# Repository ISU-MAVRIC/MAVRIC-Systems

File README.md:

# MAVRIC-Systems
The repository for the Systems Team. Contains all resources pertaining to the Systems Team, including: rover and base station code, custom PCB designs, electrical diagrams, and rover documentation. Clone this repository to your computer with Git Bash, GitHub Desktop, or another Git client to edit files. Talk to the current Systems Team Lead or the current MAVRIC Project Manager to get commit access so you can push your changes to the repository.

## Repository Structure
MAVRIC currently only maintains the Scarab code base. The code for Phoenix, our previous rover, was captured as a GitHub release and can be viewed by checking out the _Phoenix - Stable_ release, tagged `v1.0.0`. Use `git checkout v1.0.0` in Git Bash or the equivalent feature in your Git client to load the Phoenix code. Each rover's code will be tagged with a release name and version number once it is complete; this repository will otherwise reflect the code state of the most recent rover in development.

Newer code is not backwards-compatible with previous generation rovers. For example, the base station software intended for use with Scarab is not compatible with Phoenix.

## Wiki Documentation
Documentation about MAVRIC rovers, past and present, is recorded using the GitHub Wiki feature. Click the _Wiki_ tab on the MAVRIC-Systems web page to open the wiki, then use the links in the sidebar to navigate to various wiki pages. Most information is up to date and the difference should be very noticeable, but if you are not able to tell the difference between current and outdated information, ask the current Systems Team Lead about it. Remember that this repository contains documentation for multiple rovers, so information that appears outdated may simply document a different rover than the one currently being developed.

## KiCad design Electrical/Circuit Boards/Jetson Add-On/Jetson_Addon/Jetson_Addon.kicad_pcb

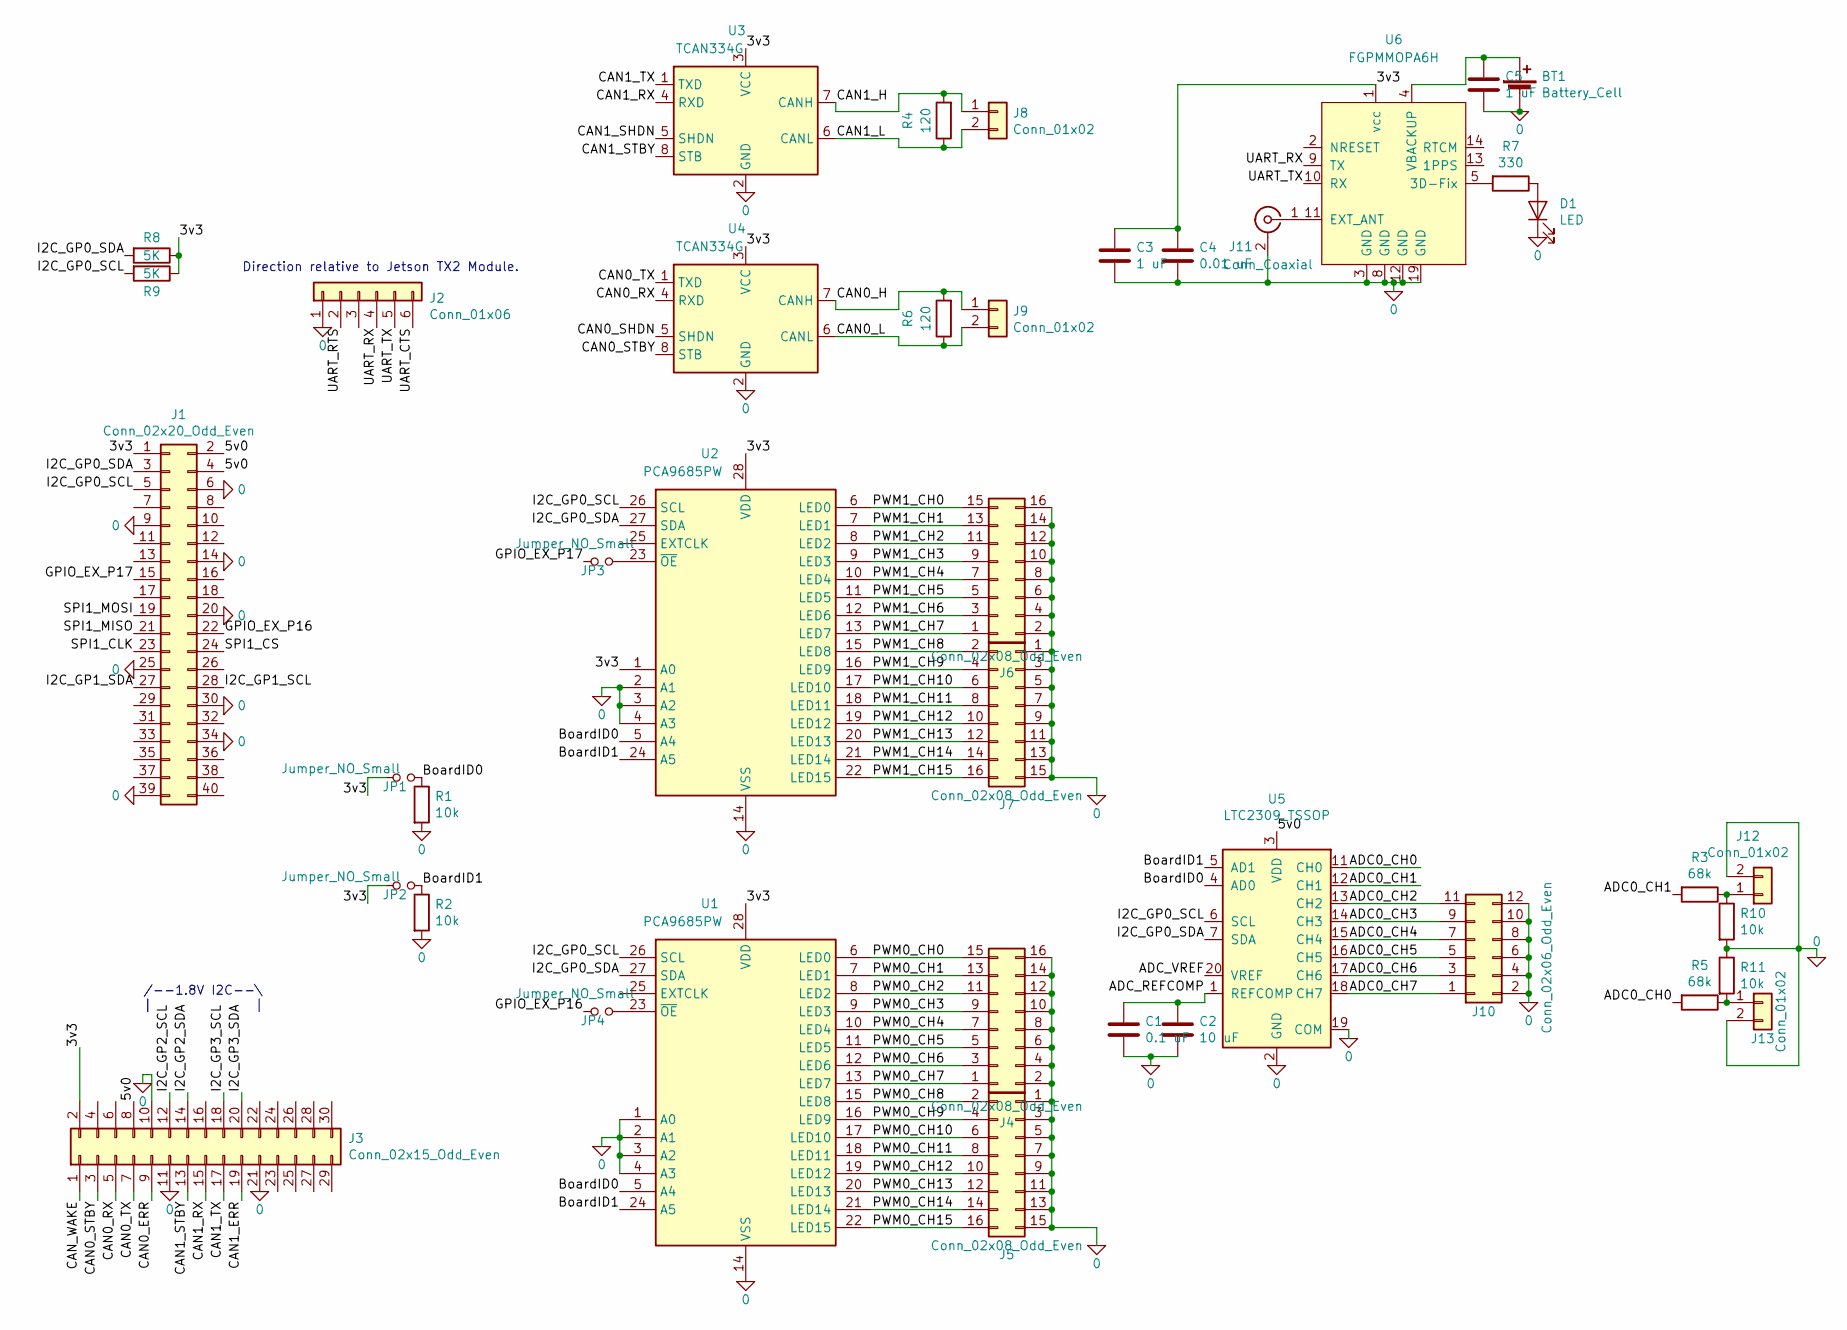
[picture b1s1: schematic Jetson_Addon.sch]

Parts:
BT1: Battery_Cell; BatteryHolder_Keystone_3000_1x12mm
C1: 0.1 uF; C_1206_3216Metric
C2: 10 uF; C_1206_3216Metric
C3, C5: 1 uF; C_0805_2012Metric
C4: 0.01 uF; C_0805_2012Metric
D1: LED; LED_1206_3216Metric
J1: Conn_02x20_Odd_Even; PinHeader_2x20_P2.54mm_Vertical
J2: Conn_01x06; PinHeader_1x06_P2.54mm_Vertical
J3: Conn_02x15_Odd_Even; PinHeader_2x15_P2.54mm_Vertical
J4, J5, J7: Conn_02x08_Odd_Even; PinHeader_2x08_P2.54mm_Vertical
J6: Conn_02x08_Odd_Even; PinHeader_2x08_P2.54mm_Horizontal
J8, J9, J12, J13: Conn_01x02; PinHeader_1x02_P2.54mm_Horizontal
J10: Conn_02x06_Odd_Even; PinHeader_2x06_P2.54mm_Horizontal
J11: Conn_Coaxial; SMA_Amphenol_132203-12_Horizontal
JP1, JP2, JP3, JP4: Jumper_NO_Small; SolderJumper-2_P1.3mm_Open_RoundedPad1.0x1.5mm
R1, R2, R10, R11: 10k; R_0805_2012Metric
R3, R5: 68k; R_0805_2012Metric
R4, R6: 120; R_0805_2012Metric
R7: 330; R_0805_2012Metric
R8, R9: 5K; R_0805_2012Metric
U1, U2: PCA9685PW; TSSOP-28_4.4x9.7mm_P0.65mm
U3, U4: TCAN334G; TSOT-23-8
U5: LTC2309_TSSOP; TSSOP-20_4.4x6.5mm_P0.65mm
U6: FGPMMOPA6H

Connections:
0: BT1.2 (-), C1.2, C2.2, C3.2, C4.2, C5.2, D1.1 (K), J1.6, J1.9, J1.14, J1.20, J1.25, J1.30, J1.34, J1.39, J2.1, J3.10, J3.11, J3.21, J4.2, J4.4, J4.6, J4.8, J4.10, J4.12, J4.14, J4.16, J5.1, J5.3, J5.5, J5.7, J5.9, J5.11, J5.13, J5.15, J6.2, J6.4, J6.6, J6.8, J6.10, J6.12, J6.14, J6.16, J7.1, J7.3, J7.5, J7.7, J7.9, J7.11, J7.13, J7.15, J10.2, J10.4, J10.6, J10.8, J10.10, J10.12, J11.2 (Ext), J12.2, J13.2, R1.2, R2.2, R10.2, R11.1, U1.1 (A0), U1.2 (A1), U1.3 (A2), U1.4 (A3), U1.14 (VSS), U2.2 (A1), U2.3 (A2), U2.4 (A3), U2.14 (VSS), U3.2 (GND), U4.2 (GND), U5.2 (GND), U5.8 (GND), U5.9 (GND), U5.19 (COM), U6.3 (GND), U6.8 (GND), U6.12 (GND), U6.19 (GND)
/3v3: C3.1, C4.1, J1.1, J3.2, JP1.1, JP2.1, R8.1, R9.1, U1.28 (VDD), U2.1 (A0), U2.28 (VDD), U3.3 (VCC), U4.3 (VCC), U6.1 (vcc)
/5v0: J1.2, J1.4, J3.8, U5.3 (VDD), U5.10 (VDD)
/ADC0_CH0: R5.2, U5.11 (CH0)
/ADC0_CH1: R3.2, U5.12 (CH1)
/ADC0_CH2: J10.11, U5.13 (CH2)
/ADC0_CH3: J10.9, U5.14 (CH3)
/ADC0_CH4: J10.7, U5.15 (CH4)
/ADC0_CH5: J10.5, U5.16 (CH5)
/ADC0_CH6: J10.3, U5.17 (CH6)
/ADC0_CH7: J10.1, U5.18 (CH7)
/ADC_REFCOMP: C1.1, C2.1, U5.1 (REFCOMP)
/ADC_VREF: U5.20 (VREF)
/BoardID0: JP1.2, R1.1, U1.5 (A4), U2.5 (A4), U5.4 (AD0)
/BoardID1: JP2.2, R2.1, U1.24 (A5), U2.24 (A5), U5.5 (AD1)
/CAN0_ERR: J3.9
/CAN0_H: J9.1, R6.2, U4.7 (CANH)
/CAN0_L: J9.2, R6.1, U4.6 (CANL)
/CAN0_RX: J3.5, U4.4 (RXD)
/CAN0_SHDN: U4.5 (SHDN)
/CAN0_STBY: J3.3, U4.8 (STB)
/CAN0_TX: J3.7, U4.1 (TXD)
/CAN1_ERR: J3.19
/CAN1_H: J8.1, R4.2, U3.7 (CANH)
/CAN1_L: J8.2, R4.1, U3.6 (CANL)
/CAN1_RX: J3.15, U3.4 (RXD)
/CAN1_SHDN: U3.5 (SHDN)
/CAN1_STBY: J3.13, U3.8 (STB)
/CAN1_TX: J3.17, U3.1 (TXD)
/CAN_WAKE: J3.1
/GPIO_EX_P16: J1.22, JP4.1
/GPIO_EX_P17: J1.15, JP3.1
/I2C_GP0_SCL: J1.5, R9.2, U1.26 (SCL), U2.26 (SCL), U5.6 (SCL)
/I2C_GP0_SDA: J1.3, R8.2, U1.27 (SDA), U2.27 (SDA), U5.7 (SDA)
/I2C_GP1_SCL: J1.28
/I2C_GP1_SDA: J1.27
/I2C_GP2_SCL: J3.12
/I2C_GP2_SDA: J3.14
/I2C_GP3_SCL: J3.18
/I2C_GP3_SDA: J3.20
/PWM0_CH0: J4.15, U1.6 (LED0)
/PWM0_CH1: J4.13, U1.7 (LED1)
/PWM0_CH2: J4.11, U1.8 (LED2)
/PWM0_CH3: J4.9, U1.9 (LED3)
/PWM0_CH4: J4.7, U1.10 (LED4)
/PWM0_CH5: J4.5, U1.11 (LED5)
/PWM0_CH6: J4.3, U1.12 (LED6)
/PWM0_CH7: J4.1, U1.13 (LED7)
/PWM0_CH8: J5.2, U1.15 (LED8)
/PWM0_CH9: J5.4, U1.16 (LED9)
/PWM0_CH10: J5.6, U1.17 (LED10)
/PWM0_CH11: J5.8, U1.18 (LED11)
/PWM0_CH12: J5.10, U1.19 (LED12)
/PWM0_CH13: J5.12, U1.20 (LED13)
/PWM0_CH14: J5.14, U1.21 (LED14)
/PWM0_CH15: J5.16, U1.22 (LED15)
/PWM1_CH0: J6.15, U2.6 (LED0)
/PWM1_CH1: J6.13, U2.7 (LED1)
/PWM1_CH2: J6.11, U2.8 (LED2)
/PWM1_CH3: J6.9, U2.9 (LED3)
/PWM1_CH4: J6.7, U2.10 (LED4)
/PWM1_CH5: J6.5, U2.11 (LED5)
/PWM1_CH6: J6.3, U2.12 (LED6)
/PWM1_CH7: J6.1, U2.13 (LED7)
/PWM1_CH8: J7.2, U2.15 (LED8)
/PWM1_CH9: J7.4, U2.16 (LED9)
/PWM1_CH10: J7.6, U2.17 (LED10)
/PWM1_CH11: J7.8, U2.18 (LED11)
/PWM1_CH12: J7.10, U2.19 (LED12)
/PWM1_CH13: J7.12, U2.20 (LED13)
/PWM1_CH14: J7.14, U2.21 (LED14)
/PWM1_CH15: J7.16, U2.22 (LED15)
/SPI1_CLK: J1.23
/SPI1_CS: J1.24
/SPI1_MISO: J1.21
/SPI1_MOSI: J1.19
/UART_CTS: J2.6
/UART_RTS: J2.2
/UART_RX: J2.4, U6.9 (TX)
/UART_TX: J2.5, U6.10 (RX)
unnamed: BT1.1 (+), C5.1, U6.4 (VBACKUP)
unnamed: D1.2 (A), R7.1
unnamed: J11.1 (In), U6.11 (EXT_ANT)
unnamed: J12.1, R3.1, R10.1
unnamed: J13.1, R5.1, R11.2
unnamed: JP3.2, U2.23 (~OE)
unnamed: JP4.2, U1.23 (~OE)
unnamed: R7.2, U6.5 (3D-Fix)

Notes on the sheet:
/--1.8V I2C--\ | |
Direction relative to Jetson TX2 Module.

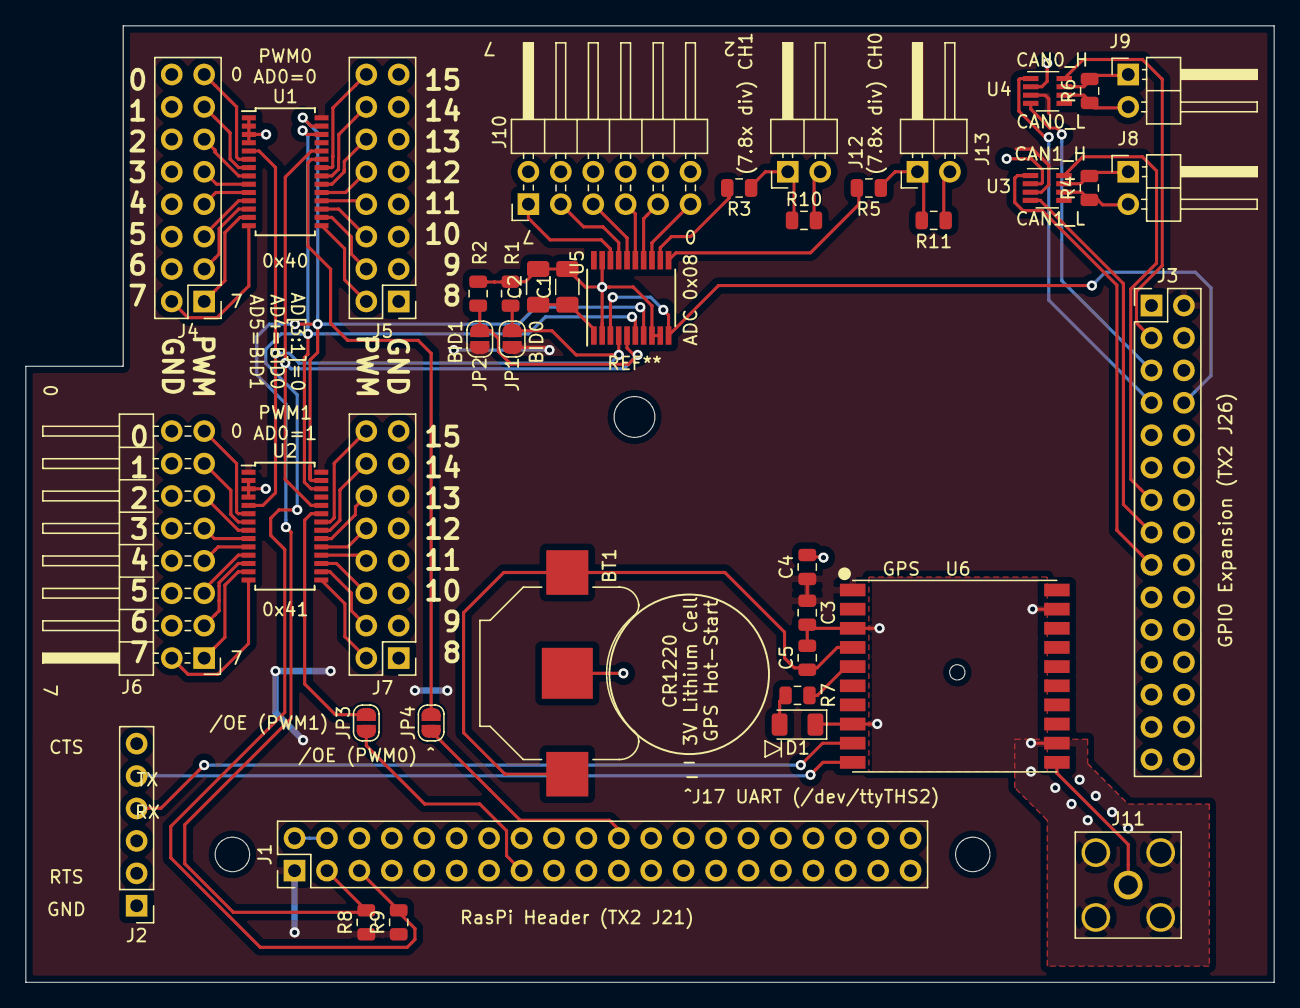
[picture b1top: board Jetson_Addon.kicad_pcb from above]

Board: 2 copper layers, 97.8 x 74.9 mm, 41 parts (0 on the bottom side), 70 nets.

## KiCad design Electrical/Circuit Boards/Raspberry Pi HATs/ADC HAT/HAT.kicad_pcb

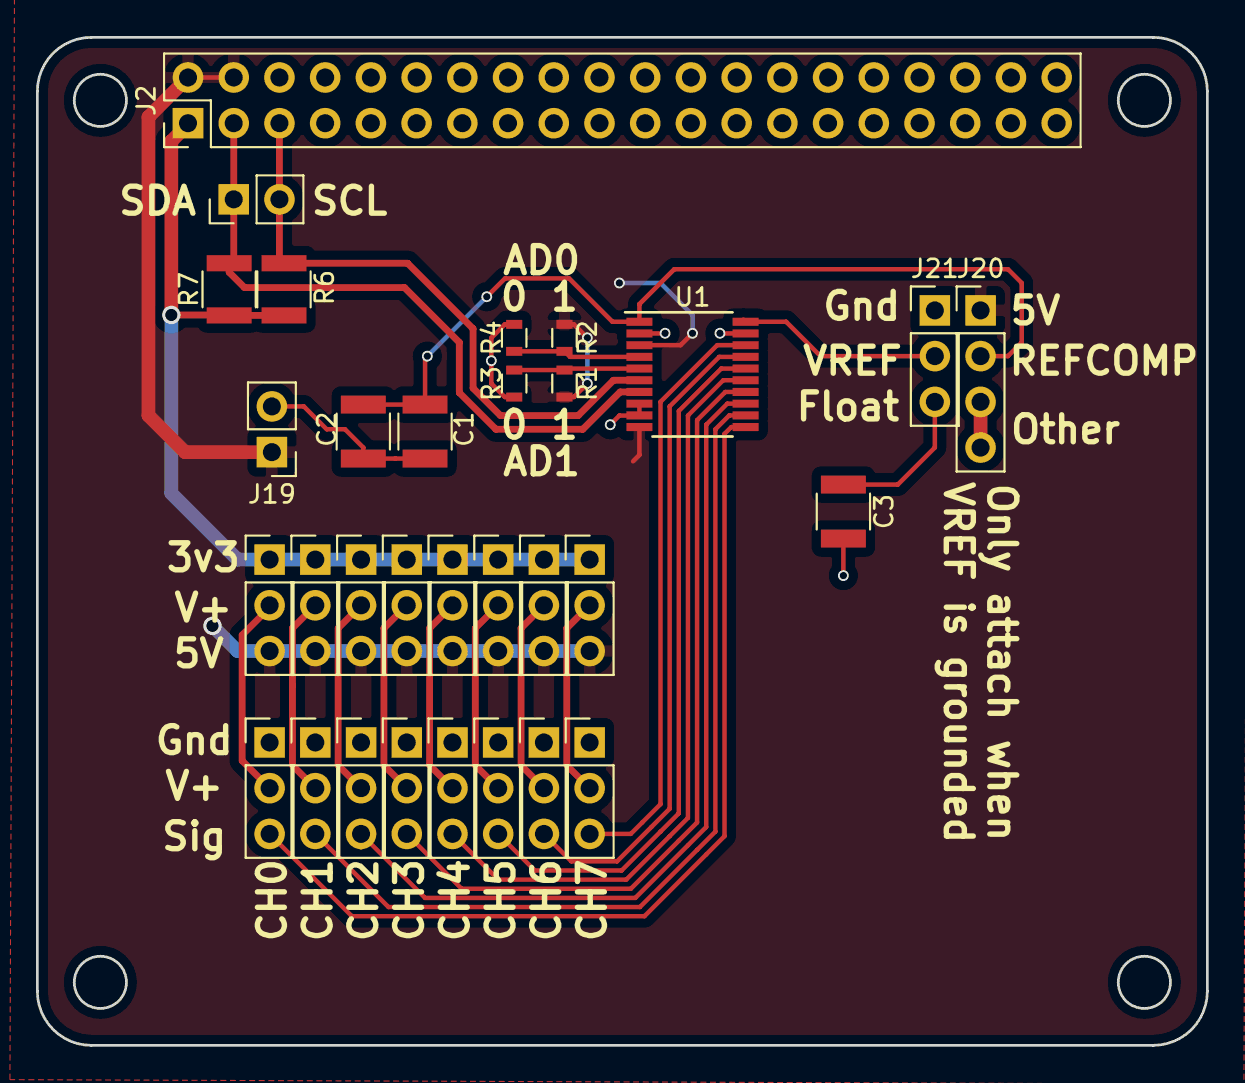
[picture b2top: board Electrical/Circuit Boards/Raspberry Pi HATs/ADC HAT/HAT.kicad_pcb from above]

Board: 2 copper layers, 65.0 x 56.0 mm, 31 parts (0 on the bottom side), 27 nets.

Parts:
C1: 0.1 uF; C_1210
C2: 10 uF; C_1210
C3: 2.2 uF; C_1210
J1, J19: CONN_01X02; Pin_Header_Straight_1x02_Pitch2.54mm
J2: CONN_02X20; Pin_Header_Straight_2x20_Pitch2.54mm
J3, J4, J5, J6, J7, J8, J9, J10, J11, J12, J13, J14, J15, J16, J17, J18: CONN_01X03; Pin_Header_Straight_1x03_Pitch2.54mm
J20: CONN_01X04_MALE; Pin_Header_Straight_1x04_Pitch2.54mm
J21: CONN_01X03_MALE; Pin_Header_Straight_1x03_Pitch2.54mm
R1, R2, R3, R4: 0; R_0603
R6, R7: 2.2K; R_1210
U1: LTC2309_TSSOP; TSSOP-20_4.4x6.5mm_Pitch0.65mm

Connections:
+3V3: J2.1, J2.17, J3.1, J4.1, J5.1, J6.1, J7.1, J8.1, J9.1, J10.1, R6.1, R7.1
+5V: J2.2, J2.4, J3.3, J4.3, J5.3, J6.3, J7.3, J8.3, J9.3, J10.3, J19.1, J20.1, R1.1, R2.1, U1.3, U1.10
/A0: J11.3, U1.11
/A1: J12.3, U1.12
/A2: J13.3, U1.13
/A3: J14.3, U1.14
/A4: J15.3, U1.15
/A5: J16.3, U1.16
/A6: J17.3, U1.17
/A7: J18.3, U1.18
/SCL: J1.2, J2.5, R6.2, U1.6
/SDA: J1.1, J2.3, R7.2, U1.7
GND: C1.2, C2.2, C3.2, J2.6, J2.9, J2.14, J2.20, J2.25, J2.30, J2.34, J2.39, J11.1, J12.1, J13.1, J14.1, J15.1, J16.1, J17.1, J18.1, J19.2, J21.1, R3.1, R4.1, U1.2, U1.8, U1.9, U1.19
unnamed: C1.1, C2.1, J20.2, U1.1
unnamed: C3.1, J21.3
unnamed: J10.2, J18.2
unnamed: J3.2, J11.2
unnamed: J4.2, J12.2
unnamed: J5.2, J13.2
unnamed: J6.2, J14.2
unnamed: J7.2, J15.2
unnamed: J8.2, J16.2
unnamed: J9.2, J17.2
unnamed: J20.3, J20.4
unnamed: J21.2, U1.20
unnamed: R1.2, R3.2, U1.5
unnamed: R2.2, R4.2, U1.4

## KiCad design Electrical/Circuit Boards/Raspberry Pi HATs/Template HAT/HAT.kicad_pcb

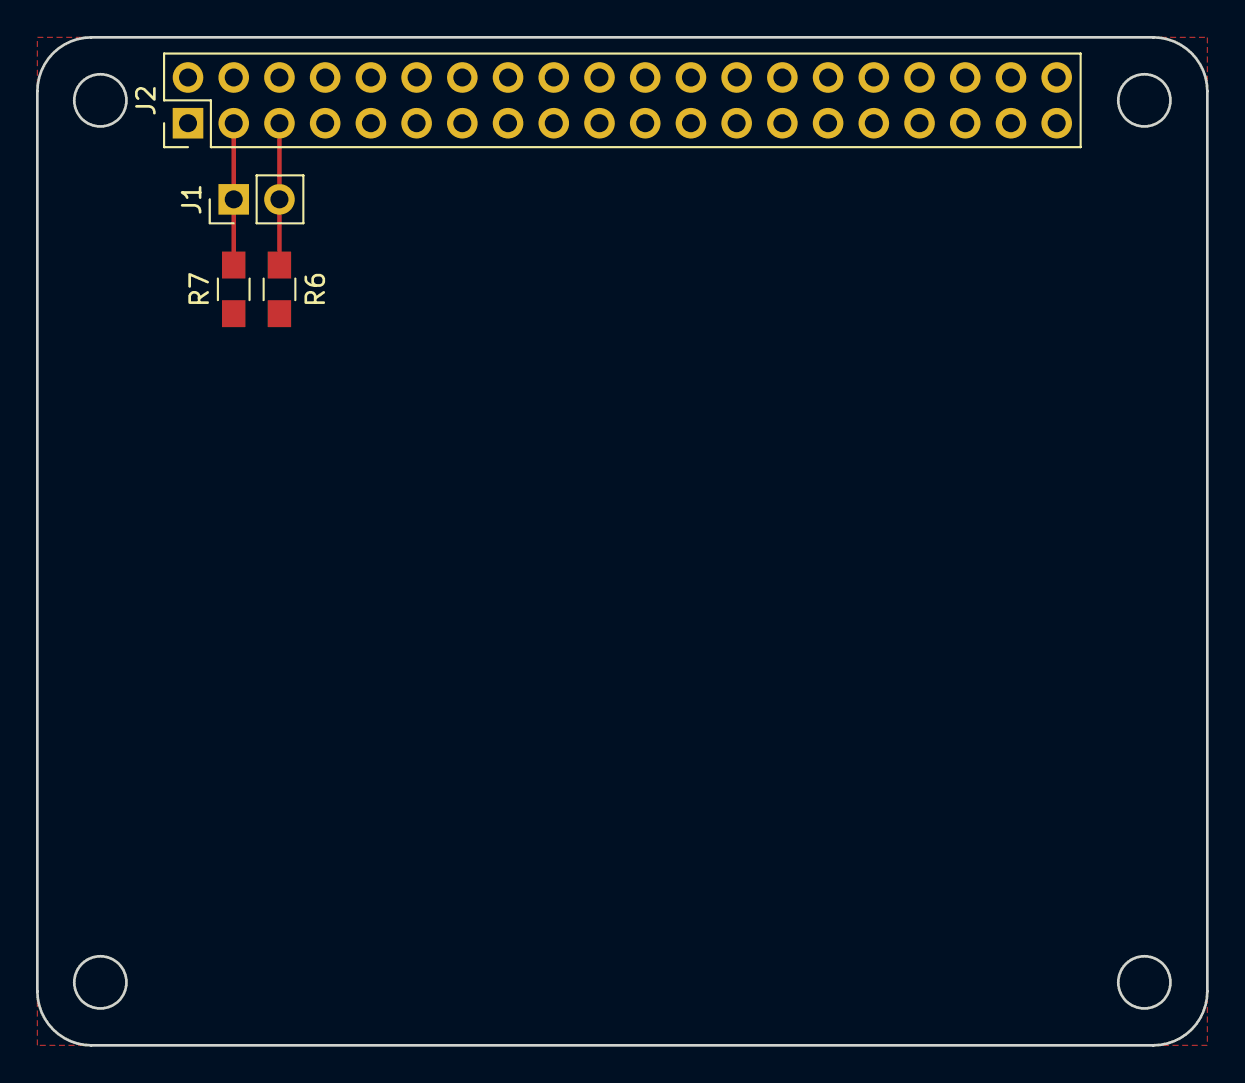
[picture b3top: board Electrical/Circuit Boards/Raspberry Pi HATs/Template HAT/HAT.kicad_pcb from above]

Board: 2 copper layers, 65.0 x 56.0 mm, 4 parts (0 on the bottom side), 5 nets.

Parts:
J1: CONN_01X02; Pin_Header_Straight_1x02_Pitch2.54mm
J2: CONN_02X20; Pin_Header_Straight_2x20_Pitch2.54mm
R6, R7: 2.2K; R_0805_HandSoldering

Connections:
+3V3: J2.1, J2.17, R6.1, R7.1
+5V: J2.2, J2.4
/SCL: J1.2, J2.5, R6.2
/SDA: J1.1, J2.3, R7.2
GND: J2.6, J2.9, J2.14, J2.20, J2.25, J2.30, J2.34, J2.39

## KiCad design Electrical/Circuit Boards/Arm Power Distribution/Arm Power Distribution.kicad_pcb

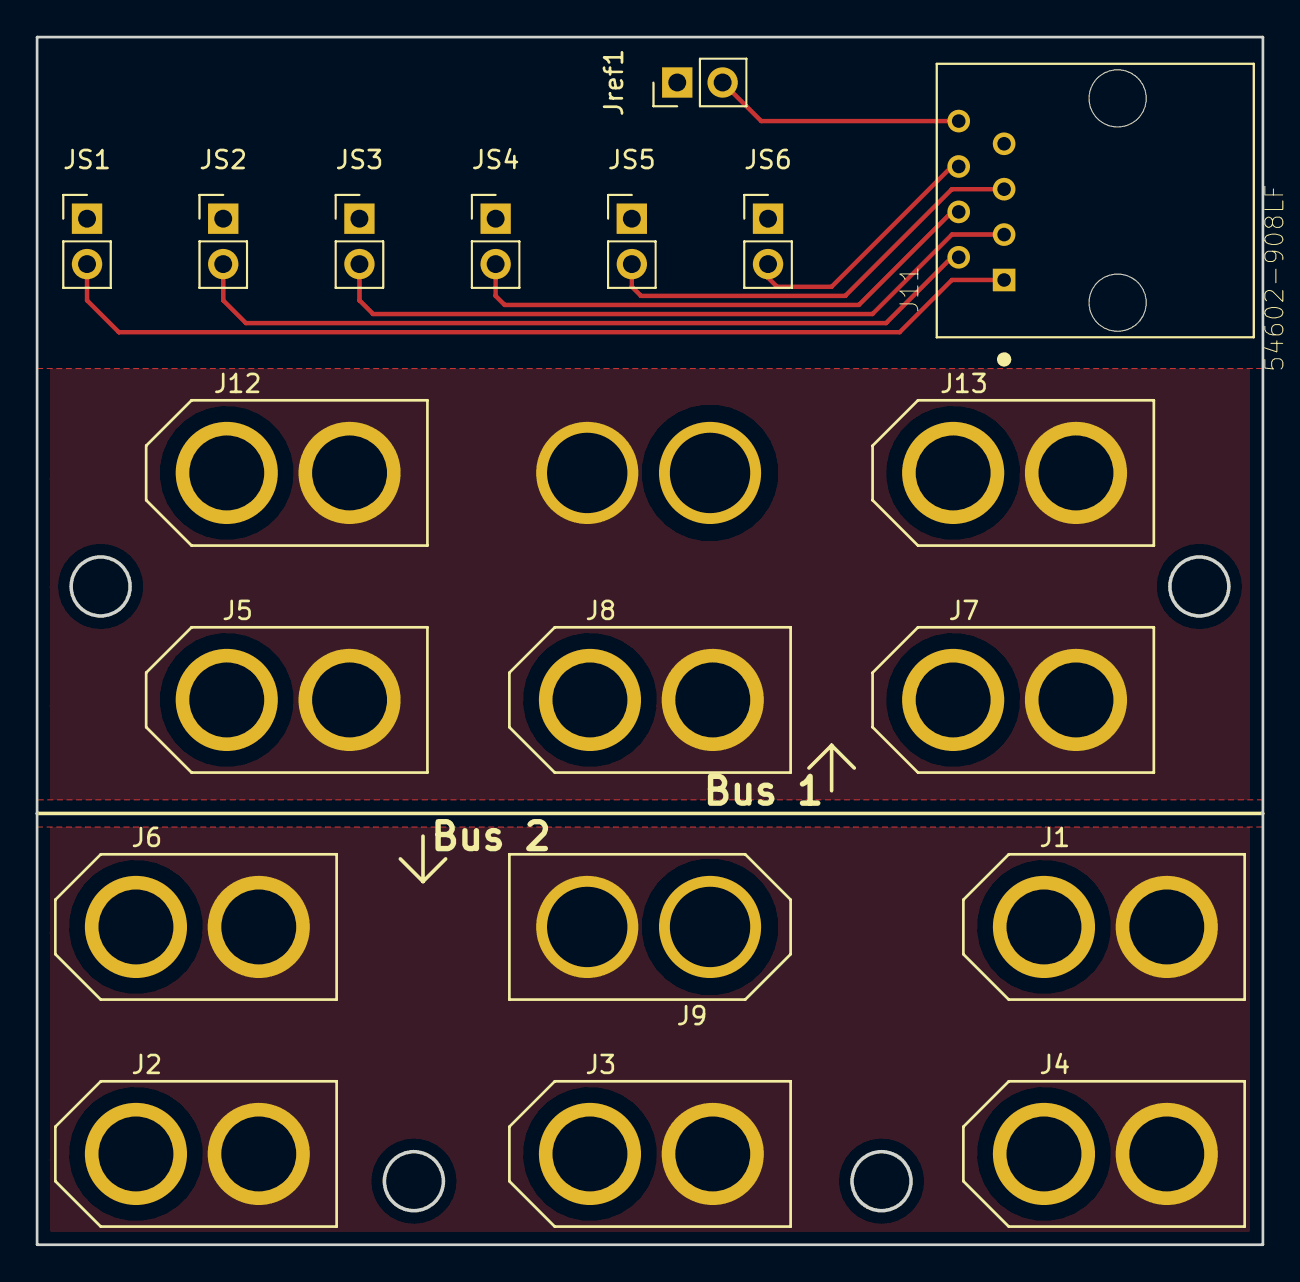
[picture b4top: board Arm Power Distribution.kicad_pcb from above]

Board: 2 copper layers, 68.6 x 67.6 mm, 20 parts (1 on the bottom side), 12 nets.

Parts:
J1, J2, J3, J4, J5, J6, J7, J8, J12, J13: XT60-F
J9, J10: XT60-M
J11: 54602-908LF; AMPHENOL_54602-908LF
JS1, JS2, JS3, JS4, JS5, JS6: CONN_01X02_MALE; Pin_Header_Straight_1x02_Pitch2.54mm
Jref1: CONN_01X02_MALE; Pin_Header_Straight_1x02_Pitch2.54mm

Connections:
/HP0: J5.1, J7.1, J8.1, J10.1, J12.1, J13.1
/HP22: J5.2, J7.2, J8.2, J10.2, J12.2, J13.2
/LP0: J1.1, J2.1, J3.1, J4.1, J6.1, J9.1
/LP12: J1.2, J2.2, J3.2, J4.2, J6.2, J9.2
unnamed: J11.1, JS1.2
unnamed: J11.2, JS2.2
unnamed: J11.3, JS3.2
unnamed: J11.4, JS4.2
unnamed: J11.5, JS5.2
unnamed: J11.6, JS6.2
unnamed: J11.7, JS1.1, JS2.1, JS3.1, JS4.1, JS5.1, JS6.1, Jref1.1
unnamed: J11.8, Jref1.2

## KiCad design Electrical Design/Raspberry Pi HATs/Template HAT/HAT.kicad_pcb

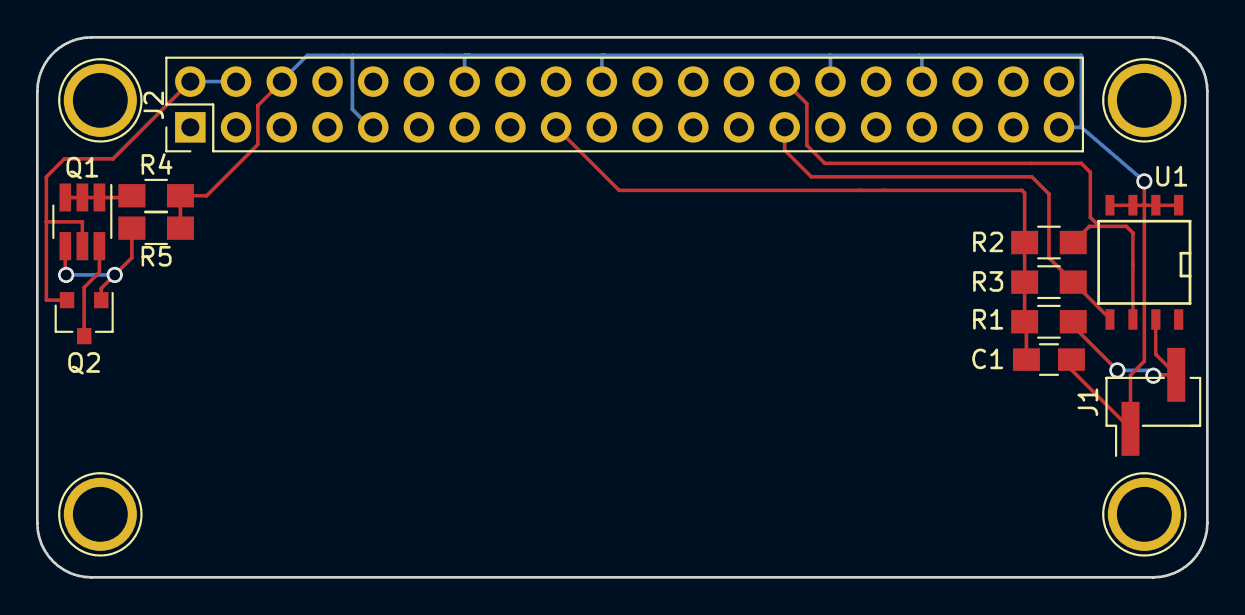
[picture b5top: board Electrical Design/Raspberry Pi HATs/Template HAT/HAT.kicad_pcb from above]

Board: 2 copper layers, 65.0 x 30.0 mm, 11 parts (0 on the bottom side), 9 nets.

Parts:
C1: 100n; C_0805_HandSoldering
J1: CONN_02X01; Pin_Header_Straight_1x02_Pitch2.54mm_SMD_Pin1Left
J2: CONN_02X20; Pin_Header_Straight_2x20_Pitch2.54mm
Q1: DMMT5401; SOT-23-6_Handsoldering
Q2: DMG2305UX; SOT-23
R1: 1K; R_0805_HandSoldering
R2, R3: 3.9K; R_0805_HandSoldering
R4: 10K; R_0805_HandSoldering
R5: 47K; R_0805_HandSoldering
U1: CAT24C32WI-GT3; SOIC-8-N

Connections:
+3V3: C1.1, J2.1, J2.17, R1.1, R2.1, R3.1
+5V: Q1.6, Q2.3
/Pi Connector/+5V_Pi: J2.2, J2.4, Q1.5, Q2.2
/Pi Connector/ID_SC: J2.28, R2.2, U1.6
/Pi Connector/ID_SD: J2.27, R3.2, U1.5
GND: C1.2, J1.1, J2.6, J2.9, J2.14, J2.20, J2.25, J2.30, J2.34, J2.39, R4.2, R5.2, U1.1, U1.2, U1.3, U1.4
unnamed: J1.2, R1.2, U1.7
unnamed: Q1.1, Q1.2, Q1.3, R4.1
unnamed: Q1.4, Q2.1, R5.1

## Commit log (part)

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2018-11-16 Added clickable autonomous map
    Added a clickable map element to the base station for sending autonomous
    waypoints. The map is centered around the rover's startup location.
2018-12-01 Added ADC hat node, untested
2018-12-01 Wrong branch
2018-12-05 Add files via upload
    Throwing error while trying to draw rover sprite in GPS box. Commented out all rover communication.
2018-12-05 Add files via upload
    Commented out communications with rover. Throwing error in function to display GPS rover
2018-12-07 Added preliminary Power distro board
    $27.6 board (2.3"x2.4" 2-layer) with 1->5 each split for 2 busses
    (intended for 22V and 12V)
2018-12-08 Added untested IMU node
    Added a node to stream IMU data from the BNO055. It has not been tested
    on the rover yet.
2018-12-10 Re-routed the ADC board (package type mistake)
2019-01-27 Rename BTC-110S.py to BTC_110S.py
2019-02-09 Add selectable ADC reference to ADC HAT
2019-02-09 Correct missing ground on C1,C2
2019-02-09 Fix silkscreen
2019-02-09 Create Spectrometer
2019-02-20 Added prototype P controller for the arm
2019-02-23 Updated arm channel connections
2019-03-09 LTS2308 HAT working (tested at 100Hz per channel, 800Hz total)
2019-04-06 Added IMU to autonomous
    Added IMU to the autonomous, to be used for heading instead of the gps.
2019-04-13 Added Arm visualization Proof of Concept
    Brooke and Christian should be able to use this to help finish the arm visualization
2019-04-13 Custom SMBus implementation of PCA9685 driver
2019-04-13 Prototype driver for bare I2C and LTC2309 (not SMBus-compatible)
2019-04-20 Initial untested state machine
    Rewrote the autonomous using a state machine model. Currently untested.
2019-04-20 Autonomous state machine fixes
2019-04-20 Update to driver for ADC with I2C python driver
2019-04-23 Tested: ROS+ADC+PWM <good> (launch is WIP)
2019-04-25 Everything (except HW) looks good in the launch file. I made some changes to make the RQT grapg more readable.
2019-04-25 Changed the namespaces a little
2019-05-04 Address and timing to ADC HAT driver
2019-05-04 All working (both PWM boards) without GPS HAT
2019-10-05 Fixes from autonomous test in May
2020-02-08 Consistency changes to get ROS running on the Jetson
2020-02-22 Added Robot Enable node to send Talon SRX heartbeat over CAN
2020-04-16 Reverted CAN_RobotEnable to default to disabled
2020-04-17 Added Jetson interface board to Git
    Included the Jetson interface board KiCAD design in the repository for
    safekeeping.
2020-09-09 Added CANable auto-start script and basic C++ test node
2020-09-17 Added CTRE Talon SRX C++ libraries and a basic C++ CAN node
2020-09-23 Update DigiKey_BOM.xlsx
    Updated interface board BOM spreadsheet
2020-09-28 Added Talon SRX firmware v4.22
2020-10-14 Add files via upload
    Library for GPS
2020-10-14 Add initial steering code to CAN drive subscriber
2020-11-22 Modified base station to work with tank-drive Scarab
2020-11-22 Rename WiringDiagram
2021-03-22 Troubleshooted drive node and sening it to rover for further testing.
2021-03-29 Finished troubleshooting test feedback.
2021-03-31 Sending completed drivetrain, drive interface, and edited cmake list and launch file for testing.
2021-04-01 Forgot to include steer train msg in drive train code.
2021-04-05 tested drive programs and got steering to work.
2021-04-05 Add base station files to git.
2021-04-14 .msg file for battery voltage
2021-04-14 Make a socket for battery voltage
2021-04-16 Modified launch and drive file for arm use. Sending to rover for troubleshooting.
2021-05-01 Science System control code
2021-09-20 Minor set up changes made when reinstalling everything.
2021-10-02 Fixed: Undefined mavric GPS msg bug
2021-10-04 Debugged drive programs
2021-10-05 Modified Drive Train to set position to zero when motor is calibrated. Also limited motors to 20% power.
2021-10-06 Fixed: Missing num satellites on gps publish
2021-10-06 Added: *.DS_Store to .gitignore
2021-10-07 Fixed: Timestamps on GPS Streamer
2021-10-11 Created library for calculating the motor speeds and postion when driving.
2021-10-12 Fixed initial commit
2021-10-12 Added: Shebang
2021-10-12 some minor updates for added comments and documentation ~untested~
2021-10-13 ubleshooted relay switcher
2021-10-15 intermediate updates
2021-10-16 Added Steer publisher initialization to auto main.
2021-10-16 Added interface to launch file.
2021-10-25 update drive toword waypoint state to have basic functionality of waypoint navigation
2021-11-02 Modified IMU code to work with I2c
2021-11-04 Trouble shooted IMU Node
2021-11-08 Added LED Control files
2021-11-09 Initial Arm PID Launch (untested)
2021-11-09 Modified jetson.launch to work with IMU and created auto laucnh file.
2021-11-13 Fixed IMU offset
2021-11-15 Fixed ramped remaps
2021-11-16 Troubleshooted autonomous and fixed gps interface.
2021-11-17 Fixed LED_Control.py
2021-11-30 Fixed boolean error
2021-12-01 Wrote and modified code for complex arm control.
2021-12-01 Update launch file
2021-12-02 Troubleshooted auto code.
2021-12-04 ubleshooted arm.
2022-02-16 Basic arUco detection
2022-02-16 Added connection string and debug print
2022-02-18 Adding current iteration of base station to github.
2022-02-19 Took manual control and calibration out of the mobile base station.
2022-02-23 Create complex main, complex globals, and pathing scripts.
2022-02-23 Removed aruco variables from basic auto.
2022-02-25 Troubleshooted complex auto.
2022-02-26 Made slight modifications to complex auto.
2022-02-28 tested complex autonomous.
2022-03-08 Troubleshooted mobile base station.
2022-03-08 Troubleshooted encoder streamer.
2022-03-11 Troubleshooted PID test. Found some decent K constants and found some issues with encoder feedback.
2022-03-11 Optimized encoder feedback.
2022-03-29 Created test launch file for manual testbench controls.
2022-04-22 ubleshooted complex auto and lightpole.
2022-04-22 Add Abe's object detection code.
2022-04-28 nor rover troubleshooting.# On branch Complex-Auto
2022-04-30 Troubleshooted autonomous system.
2022-05-02 rewrote encoder feedback code to work with jetson GPIO library.
2022-05-07 uble shooted.
2022-05-10 Did some auto test runs, modified some code.
2022-05-24 Added: Pixel location and camera type to Complex Auto globals
2022-05-26 Added dedicated debug topic and interface to stream auto data to base station. Also wrote drive sim which simulates GPS and IMU data.
2022-05-28 Wrote Object Detection Node
2022-05-28 Troubleshooted arm utils.
2022-05-30 ubleshooted
2022-05-30 ubleshoot
2022-08-24 Uploading current base station.
2022-10-04 Created script to test motor motion via can bus
2022-10-09 ubleshooted test codes.
2022-10-20 Initial ESC heartbeat code (Untested)
2022-11-03 Added: velocity and percent output control
2022-11-08 Finished all function relating to sending can messages.
2022-11-09 Troubleshooted, got feedback fuctions working.
2022-11-10 Debug
2022-12-04 Added Gabe's Spark max drive train.
2022-12-04 Changed drive motor scale to convert ft/s to
2022-12-06 Added: Shoulder pitch support
2023-02-17 Updated wheelbase for better turning
2023-02-21 fixed CMake file. Shoulder Pitch works now!
2023-02-22 Fixing Jacob's commit
2023-02-24 various things disabled, check comments
2023-02-24 Claw Servo actuation added to expo.launch
2023-02-27 reversed pitch controls
2023-02-27 increased scales
2023-02-28 Added neepixel library
2023-03-01 testing
2023-03-01 added drive to auto.launch, commented out gps
2023-03-01 config new defaults for auto_globals +new entr msg
2023-03-01 changed base station controls to be more natural
2023-03-01 readded camera control
2023-03-01 reorganised groups in launch file
2023-03-01 added GPS Sim to auto.launch, updated rover size
2023-03-02 using rock candy controller now
2023-03-02 outdoor testing
2023-03-21 State Indicator added for Complex Auto
2023-04-05 Updated: Removed serial permissions
2023-04-21 Removed: Old launch files
2023-04-21 Removed: Voltage Monitor & Interface
2023-04-21 Removed: Phoenix GUI
2023-04-21 Removed: Temp Monitoring
2023-04-25 Added new wiring diagrams
    sorry bout bypassing, I don't think a .png will break anything
2023-04-29 added neopixel testing and adafruit board
2023-09-20 upgrade to ros noetic, suppressed arm catkin build
2023-09-21 fix catkin_build. Noetic Fully installed!
2023-09-23 converted SP and EP to sparkmax
2023-09-23 finished all axis, awaiting testing
2023-09-28 changed drive magnitude by 100
2023-09-29 windows/linux switcher
2023-10-06 fixing merge issues
2023-10-09 Created HTTP camera script
2023-10-09 started BNO055 Calibration script
2023-10-14 base station testing
2023-10-19 Update HTTP_Cam.py with ROS params
2023-10-19 Added arm camera params to expo.launch
2023-10-19 Revert "led test code with export env"
    This reverts commit 97c5f2826fa98399b3dd90a31399ce1427c1d2b8.
2023-10-19 added ledtest.py with env changes
2023-10-23 committing akwasi's changes
2023-10-24 removed debug images
2023-10-24 saving colin's progress since he didn't commit
2023-10-28 init and basic interface working
2023-10-31 adding rounding
2023-10-31 akwasi's monday work
2023-11-03 remove arm from launch
2023-11-04 integrated mode switching
2023-11-06 debug with gabe
2023-11-10 documented 900 mhz interface
2023-11-11 initial attempt
2023-11-14 integrate with ros
2023-11-14 rename file and add to sensor launch
2023-11-14 added volts per cell
2023-11-15 reworked drive so only one script accesses can bus
2023-11-15 changed topic assignments for testing
2023-11-15 undoing lora deletion
2023-11-28 changed debug statements
2023-11-28 Delete src/mavric/src/RTSP_Camera.py
    File is no longer needed, as the camera runs from HTTP script.
2023-11-28 Update expo.launch
    Removed the additional camera node as it was for testing purposes.
2023-11-29 integrated camera change
2023-12-02 add lid control
2023-12-04 in-lab testing
2023-12-06 Update Sensors.launch w respawn
2024-02-03 IMU work and auto_launch testing
2024-02-10 removed manual state ind, now pub automatically. Reworked waypoints
2024-02-10 fixing a few small things
2024-02-13 Reworked drive math to output values for v and ang
2024-02-14 json waypoint interpreter and bool enable
2024-02-15 reworked waypoint handling on rover to a bi-directional, single topic
2024-02-15 deleted complex autonomous
2024-02-15 cleaning up lots of old junk
2024-02-16 some small fixes to gps geodesic calculation and more led debug
2024-02-20 Added point drive and comments.
2024-02-21 committing jackson's work
2024-02-21 editing autonomous drive math
2024-02-21 finished drivemath conversion
2024-02-22 finished steering code
2024-02-22 changed motor directions and scales
2024-02-22 autonomous testing
2024-02-22 arm testing and final gps modifications
2024-02-24 updated some constants
2024-02-24 autonomous outdoor testing
2024-03-24 new ros dependency
2024-03-24 test launch file
2024-03-30 implemented BNO085 into our code
2024-04-06 start of script
2024-04-06 positon feedback fixed and swab position snapping now works!
2024-04-11 started basic features for aruco tag finder state
2024-04-13 saturday testing
2024-04-15 Distance calc ready for testing
2024-04-17 added new angles calculation and some comments about functions
2024-04-17 created initial driveTowardTag state
2024-04-20 updated calibration constants with on rover calibration values
2024-04-20 nvm its bad
2024-04-20 pushed jackson's work and some of my edits
2024-04-23 non driving debug testing
2024-04-25 deleting arucotest
2024-04-25 not sure how these missed the code purge
2024-05-01 deleted test file
2024-05-14 added teleop toggle
2024-05-21 created an action script to capture a panoramic
2024-05-21 removing old unused launch files
2024-05-21 bye bye phoenix code
2024-05-21 more phoenix removed
2024-05-22 fixed launch file kerfuffle
2024-05-24 undo testing comments
2024-05-27 day 4 testing
2024-05-28 dawn of the final day testing. Added drill controls
2024-05-30 auto testing competition. new override for led
